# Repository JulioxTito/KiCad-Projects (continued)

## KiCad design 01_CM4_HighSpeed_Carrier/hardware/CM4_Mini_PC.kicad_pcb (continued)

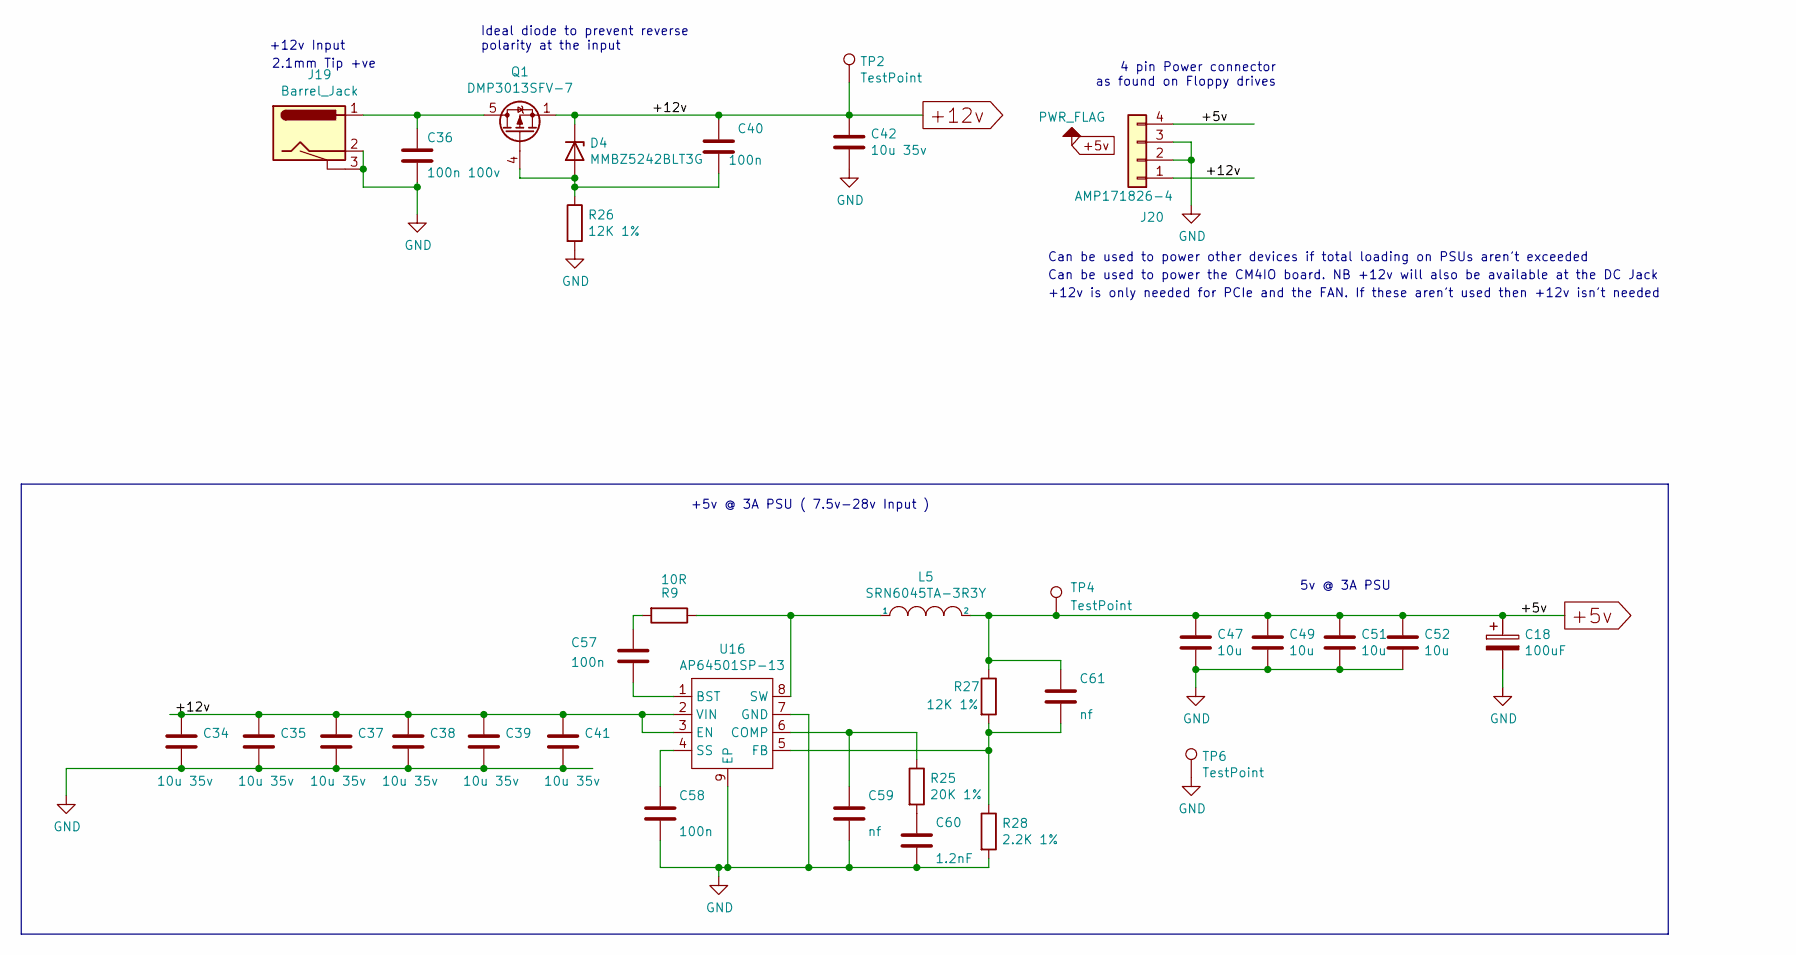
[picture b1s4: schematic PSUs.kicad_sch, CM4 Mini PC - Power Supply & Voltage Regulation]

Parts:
C18: 100uF; CP_EIA-7343-31_Kemet-D; Part Description Capacitor, SP-Cap, 100u, 6.3V, 15mR ESR
C34, C35, C37, C38, C39, C41, C42: 10u 35v; C_0805_2012Metric; Part Description 10uF 10% or 20% 35V Ceramic Capacitor X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
C36: 100n 100v; C_0402_1005Metric; Part Description 0.1uF 10% 100V Ceramic Capacitor X5R 04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
C40, C57, C58: 100n; C_0402_1005Metric; Part Description 0.1uF 10% 16V Ceramic Capacitor X7R 040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
C47, C49, C51, C52: 10u; C_0805_2012Metric; Part Description 10uF 10% 10V Ceramic Capacitor X7R 0805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
C59: nf; C_0402_1005Metric
C60: 1.2nF; C_0402_1005Metric; Part Description 1200pF 10% 10V Ceramic Capacitor X5R 04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
C61: nf; C_0402_1005Metric; Part Description 220 pF, 50 V, 0402 [1005 Metric], ± 5%,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
D4: MMBZ5242BLT3G; SOT-23; Part Description Zener Diode 12V 225mW 5% Surface Mount 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
J19: Barrel_Jack; BarrelJack_Horizontal; Part Description DC Power Connectors PCB 2.1MM
J20: AMP171826-4; PinHeader_1x04_P2.54mm_Vertical; Part Description Wire-To-Board Connector, Right Angle, 2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
L5: SRN6045TA-3R3Y; L_Bourns_SRN6045TA; Part Description 3.3µH Semi-Shielded Wirewound Inductor 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
Q1: DMP3013SFV-7; Diodes_PowerDI3333-8; Part Description DMP3013SFV-7 - Power MOSFET, P Channel,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
R9: 10R; R_0402_1005Metric; Part Description Resistor 10R M1005 1% 63mW
R25: 20K 1%; R_0402_1005Metric; Part Description Resistor 20K M1005 1% 63mW
R26, R27: 12K 1%; R_0402_1005Metric; Part Description Resistor 12K M1005 1% 63mW
R28: 2.2K 1%; R_0402_1005Metric; Part Description Resistor 2.2K M1005 1% 63mW
TP2, TP4, TP6: TestPoint; TestPoint_Pad_2.0x2.0mm
U16: AP64501SP-13; SOIC-8-1EP_3.9x4.9mm_P1.27mm_EP2.95x4.9mm_Mask2.71x3.4mm_Th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; Part Description Buck Switching Regulator IC Positive Ad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

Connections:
+5v: C18.1, C47.1, C49.1, C51.1, C52.1, C61.1, J20.4, L5.2, R27.1, TP4.1 (1_1); also elsewhere on the board
+12v: C34.1, C35.1, C37.1, C38.1, C39.1, C40.1, C41.1, C42.1, D4.1 (K), J20.1, Q1.1 (S), Q1.2 (S), Q1.3 (S), TP2.1 (1_1), U16.2 (VIN), U16.3 (EN); also elsewhere on the board
GND: C18.2, C34.2, C35.2, C36.2, C37.2, C38.2, C39.2, C41.2, C42.2, C47.2, C49.2, C51.2, C52.2, C58.2, C59.2, C60.2, J19.2, J19.3, J20.2, J20.3, R26.2, R28.2, TP6.1 (1_1), U16.7 (GND), U16.9 (EP); also elsewhere on the board
unnamed: C57.1, R9.2
unnamed: C60.1, R25.2
unnamed: C40.2, D4.2 (A), Q1.4 (G), R26.1
unnamed: C36.1, J19.1, Q1.5 (D)
unnamed: C57.2, U16.1 (BST)
unnamed: C59.1, R25.1, U16.6 (COMP)
unnamed: C61.2, R27.2, R28.1, U16.5 (FB)
unnamed: C58.1, U16.4 (SS)
unnamed: L5.1, R9.1, U16.8 (SW)

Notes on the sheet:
+12v Input
Can be used to power other devices if total loading on PSUs aren't exceeded
5v @ 3A PSU
+12v is only needed for PCIe and the FAN. If these aren't used then +12v isn't needed
Can be used to power the CM4IO board. NB +12v will also be available at the DC Jack
2.1mm Tip +ve
Ideal diode to prevent reverse polarity at the input
4 pin Power connector as found on Floppy drives
+5v @ 3A PSU ( 7.5v-28v Input )

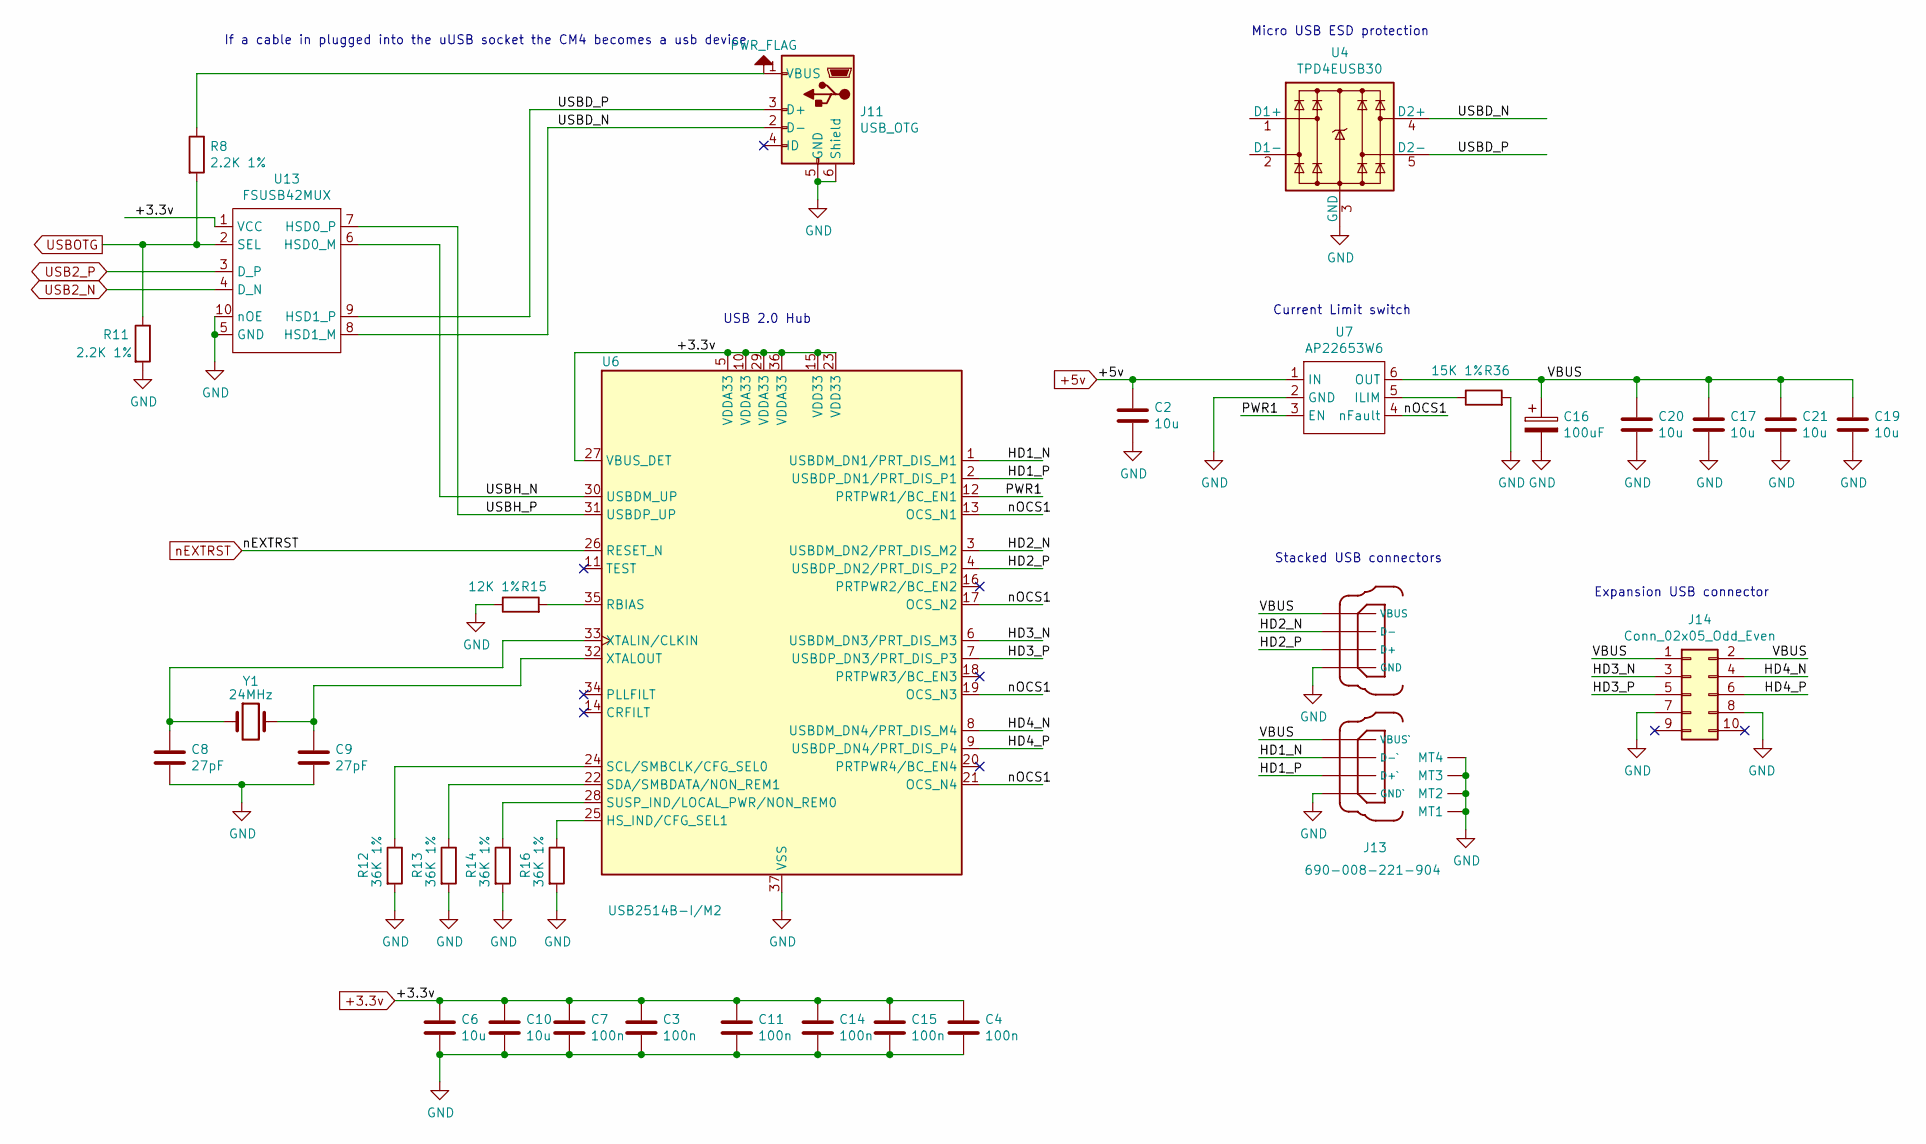
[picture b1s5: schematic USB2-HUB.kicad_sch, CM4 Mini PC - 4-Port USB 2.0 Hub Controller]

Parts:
C2, C6, C10, C17, C19, C20, C21: 10u; C_0805_2012Metric; Part Description 10uF 10% 10V Ceramic Capacitor X7R 0805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
C3, C4, C7, C11, C14, C15: 100n; C_0402_1005Metric; Part Description 0.1uF 10% 16V Ceramic Capacitor X7R 040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
C8, C9: 27pF; C_0402_1005Metric; Part Description 27pF 5% 50V Ceramic Capacitor C0G, NP0 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
C16: 100uF; CP_EIA-7343-31_Kemet-D; Part Description Capacitor, SP-Cap, 100u, 6.3V, 15mR ESR
J11: USB_OTG; USB_Micro-B_EDAC_UCON00686; Part Description USB - micro B USB 2.0 Receptacle Connec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
J13: 690-008-221-904; MOLEX_USB_67298-4090; Part Description USB-A (USB TYPE-A), Stacked Receptacle 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
J14: Conn_02x05_Odd_Even; PinHeader_2x05_P2.54mm_Vertical; Part Description PinHeader_2x05_P2.54mm_Vertical
R8, R11: 2.2K 1%; R_0402_1005Metric; Part Description Resistor 2.2K M1005 1% 63mW
R12, R13, R14, R16: 36K 1%; R_0402_1005Metric; Part Description Resistor 36K M1005 1% 63mW
R15: 12K 1%; R_0402_1005Metric; Part Description Resistor 12K M1005 1% 63mW
R36: 15K 1%; R_0402_1005Metric; Part Description Resistor 15K M1005 1% 63mW
U4: TPD4EUSB30; USON-10_2.5x1.0mm_P0.5mm; Part Description Quad TVS diode for high speed signals (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
U6: USB2514B-I/M2; QFN-36-1EP_6x6mm_P0.5mm_EP3.7x3.7mm; Part Description USB Hub Controller USB Interface 36-SQF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
U7: AP22653W6; SOT-23-6; Part Description Power Switch/Driver 1:1 P-Channel 2.1A 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
U13: FSUSB42MUX; MSOP-10_3x3mm_P0.5mm; Part Description USB Switch IC 1 Channel 10-MSOP
Y1: 24MHz; Crystal_SMD_HC49-SD; Part Description 24MHz Crystal 18pf 30ppm 30ppm

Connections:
+3.3v: C3.1, C4.1, C6.1, C7.1, C10.1, C11.1, C14.1, C15.1, U6.5 (VDDA33), U6.10 (VDDA33), U6.15 (VDD33), U6.23 (VDD33), U6.27 (VBUS_DET), U6.29 (VDDA33), U6.36 (VDDA33), U13.1 (VCC); also elsewhere on the board
+5v: C2.1, U7.1 (IN); also elsewhere on the board
/USB_Hub_Subsystem/HD1_N: J13.2 (D-`), U6.1 (USBDM_DN1/PRT_DIS_M1)
/USB_Hub_Subsystem/HD1_P: J13.3 (D+`), U6.2 (USBDP_DN1/PRT_DIS_P1)
/USB_Hub_Subsystem/HD2_N: J13.6 (D-), U6.3 (USBDM_DN2/PRT_DIS_M2)
/USB_Hub_Subsystem/HD2_P: J13.7 (D+), U6.4 (USBDP_DN2/PRT_DIS_P2)
/USB_Hub_Subsystem/HD3_N: J14.3, U6.6 (USBDM_DN3/PRT_DIS_M3)
/USB_Hub_Subsystem/HD3_P: J14.5, U6.7 (USBDP_DN3/PRT_DIS_P3)
/USB_Hub_Subsystem/HD4_N: J14.4, U6.8 (USBDM_DN4/PRT_DIS_M4)
/USB_Hub_Subsystem/HD4_P: J14.6, U6.9 (USBDP_DN4/PRT_DIS_P4)
/USB_Hub_Subsystem/PWR1: U6.12 (PRTPWR1/BC_EN1), U7.3 (EN)
/USB_Hub_Subsystem/USBD_N: J11.2 (D-), U4.4 (D2+), U4.7, U13.8 (HSD1_M)
/USB_Hub_Subsystem/USBD_P: J11.3 (D+), U4.5 (D2-), U4.6, U13.9 (HSD1_P)
/USB_Hub_Subsystem/USBH_N: U6.30 (USBDM_UP), U13.6 (HSD0_M)
/USB_Hub_Subsystem/USBH_P: U6.31 (USBDP_UP), U13.7 (HSD0_P)
/USB_Hub_Subsystem/VBUS: C16.1, C17.1, C19.1, C20.1, C21.1, J13.1 (VBUS`), J13.5 (VBUS), J14.1, J14.2, U7.6 (OUT)
/USB_Hub_Subsystem/nOCS1: U6.13 (OCS_N1), U6.17 (OCS_N2), U6.19 (OCS_N3), U6.21 (OCS_N4), U7.4 (nFault)
GND: C2.2, C3.2, C4.2, C6.2, C7.2, C8.2, C9.2, C10.2, C11.2, C14.2, C15.2, C16.2, C17.2, C19.2, C20.2, C21.2, J11.5 (GND), J11.6 (Shield), J13.4 (GND`), J13.8 (GND), J13.MT1, J13.MT2, J13.MT3, J13.MT4, J14.7, J14.8, R11.2, R12.2, R13.2, R14.2, R15.1, R16.2, R36.2, U4.3 (GND), U4.8 (GND), U6.37 (VSS), U7.2 (GND), U13.5 (GND), U13.10 (nOE); also elsewhere on the board
unnamed: J11.1 (VBUS), R8.1
unnamed: U4.1 (D1+), U4.10
unnamed: U4.2 (D1-), U4.9
unnamed: R16.1, U6.25 (HS_IND/CFG_SEL1)
unnamed: R15.2, U6.35 (RBIAS)
unnamed: R12.1, U6.24 (SCL/SMBCLK/CFG_SEL0)
unnamed: R13.1, U6.22 (SDA/SMBDATA/NON_REM1)
unnamed: R14.1, U6.28 (SUSP_IND/LOCAL_PWR/NON_REM0)
unnamed: C8.1, U6.33 (XTALIN/CLKIN), Y1.1
unnamed: C9.1, U6.32 (XTALOUT), Y1.2
unnamed: R36.1, U7.5 (ILIM)
USB2_N: U13.4 (D_N); also elsewhere on the board
USB2_P: U13.3 (D_P); also elsewhere on the board
USBOTG: R8.2, R11.1, U13.2 (SEL)
nEXTRST: U6.26 (RESET_N); also elsewhere on the board

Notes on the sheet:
Expansion USB connector
Current Limit switch
USB 2.0 Hub
If a cable in plugged into the uUSB socket the CM4 becomes a usb device
Micro USB ESD protection
Stacked USB connectors

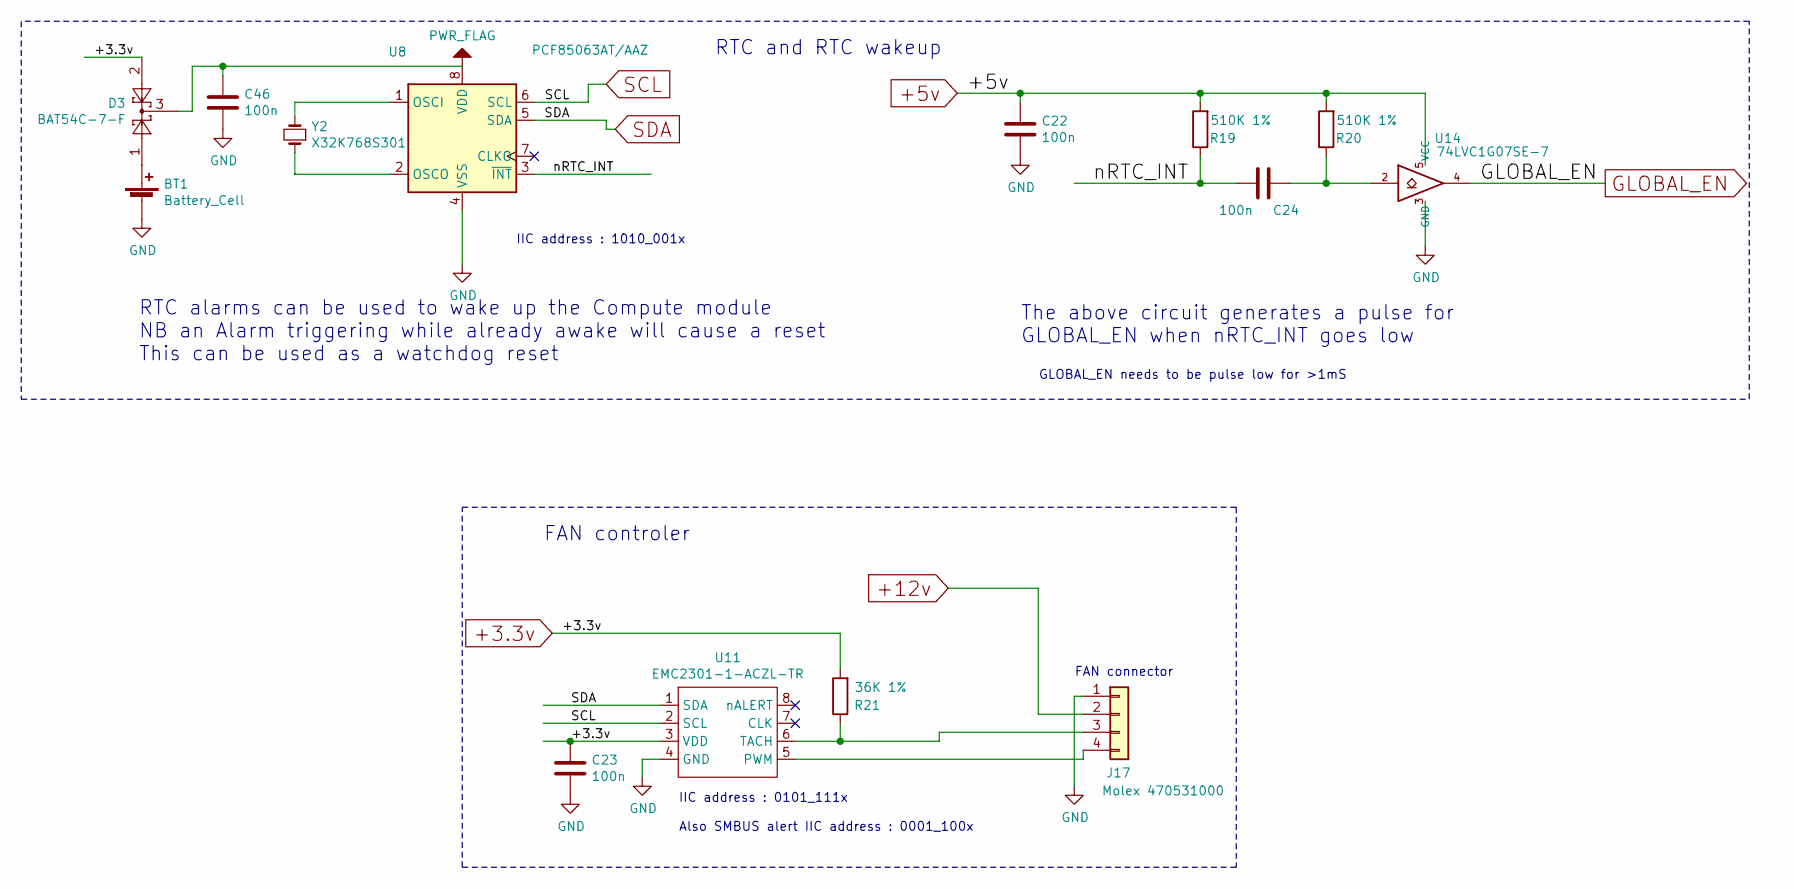
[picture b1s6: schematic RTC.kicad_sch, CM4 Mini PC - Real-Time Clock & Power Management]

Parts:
BT1: Battery_Cell; BatteryHolder_Keystone_3034_1x20mm; Part Description Battery Retainer Coin, 20.0mm 1 Cell SM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
C22, C23, C24, C46: 100n; C_0402_1005Metric; Part Description 0.1uF 10% 16V Ceramic Capacitor X7R 040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
D3: BAT54C-7-F; SOT-23; Part Description Diode Array 1 Pair Common Cathode Schot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
J17: Molex 470531000; FanPinHeader_1x04_P2.54mm_Vertical; Part Description Connector Header Through Hole 4 positio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
R19, R20: 510K 1%; R_0402_1005Metric; Part Description Resistor 510K M1005 1% 63mW
R21: 36K 1%; R_0402_1005Metric; Part Description Resistor 36K M1005 1% 63mW
U8: PCF85063AT/AAZ; SOIC-8_3.9x4.9mm_P1.27mm; Part Description Real Time Clock (RTC) IC Clock/Calendar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
U11: EMC2301-1-ACZL-TR; MSOP-8_3x3mm_P0.65mm; Part Description Motor Driver PWM 8-MSOP
U14: 74LVC1G07SE-7; SOT-353_SC-70-5; Part Description Buffer, Non-Inverting 1 Element 1 Bit p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
Y2: X32K768S301; Crystal_SMD_3215-2Pin_3.2x1.5mm; Part Description Crystal 32.768KHz 7pF 20pmm

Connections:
+3.3v: C23.1, D3.2, R21.2, U11.3 (VDD); also elsewhere on the board
+5v: C22.1, R19.2, R20.2, U14.5 (VCC); also elsewhere on the board
+12v: J17.2; also elsewhere on the board
/Real_Time_Clock/nRTC_INT: C24.2, R19.1, U8.3 (~INT)
GLOBAL_EN: U14.4; also elsewhere on the board
GND: BT1.2 (-), C22.2, C23.2, C46.2, J17.1, U8.4 (VSS), U11.4 (GND), U14.3 (GND); also elsewhere on the board
unnamed: BT1.1 (+), D3.1
unnamed: C24.1, R20.1, U14.2
unnamed: J17.3, R21.1, U11.6 (TACH)
unnamed: J17.4, U11.5 (PWM)
unnamed: U8.1 (OSCI), Y2.2
unnamed: U8.2 (OSCO), Y2.1
unnamed: C46.1, D3.3, U8.8 (VDD)
SCL: U8.6 (SCL), U11.2 (SCL)
SDA: U8.5 (SDA), U11.1 (SDA)

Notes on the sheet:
RTC alarms can be used to wake up the Compute module NB an Alarm triggering while already awake will cause a reset This can be used as a watchdog reset
RTC and RTC wakeup
Also SMBUS alert IIC address : 0001_100x
IIC address : 0101_111x
IIC address : 1010_001x
GLOBAL_EN needs to be pulse low for >1mS
FAN controler
FAN connector
The above circuit generates a pulse for GLOBAL_EN when nRTC_INT goes low

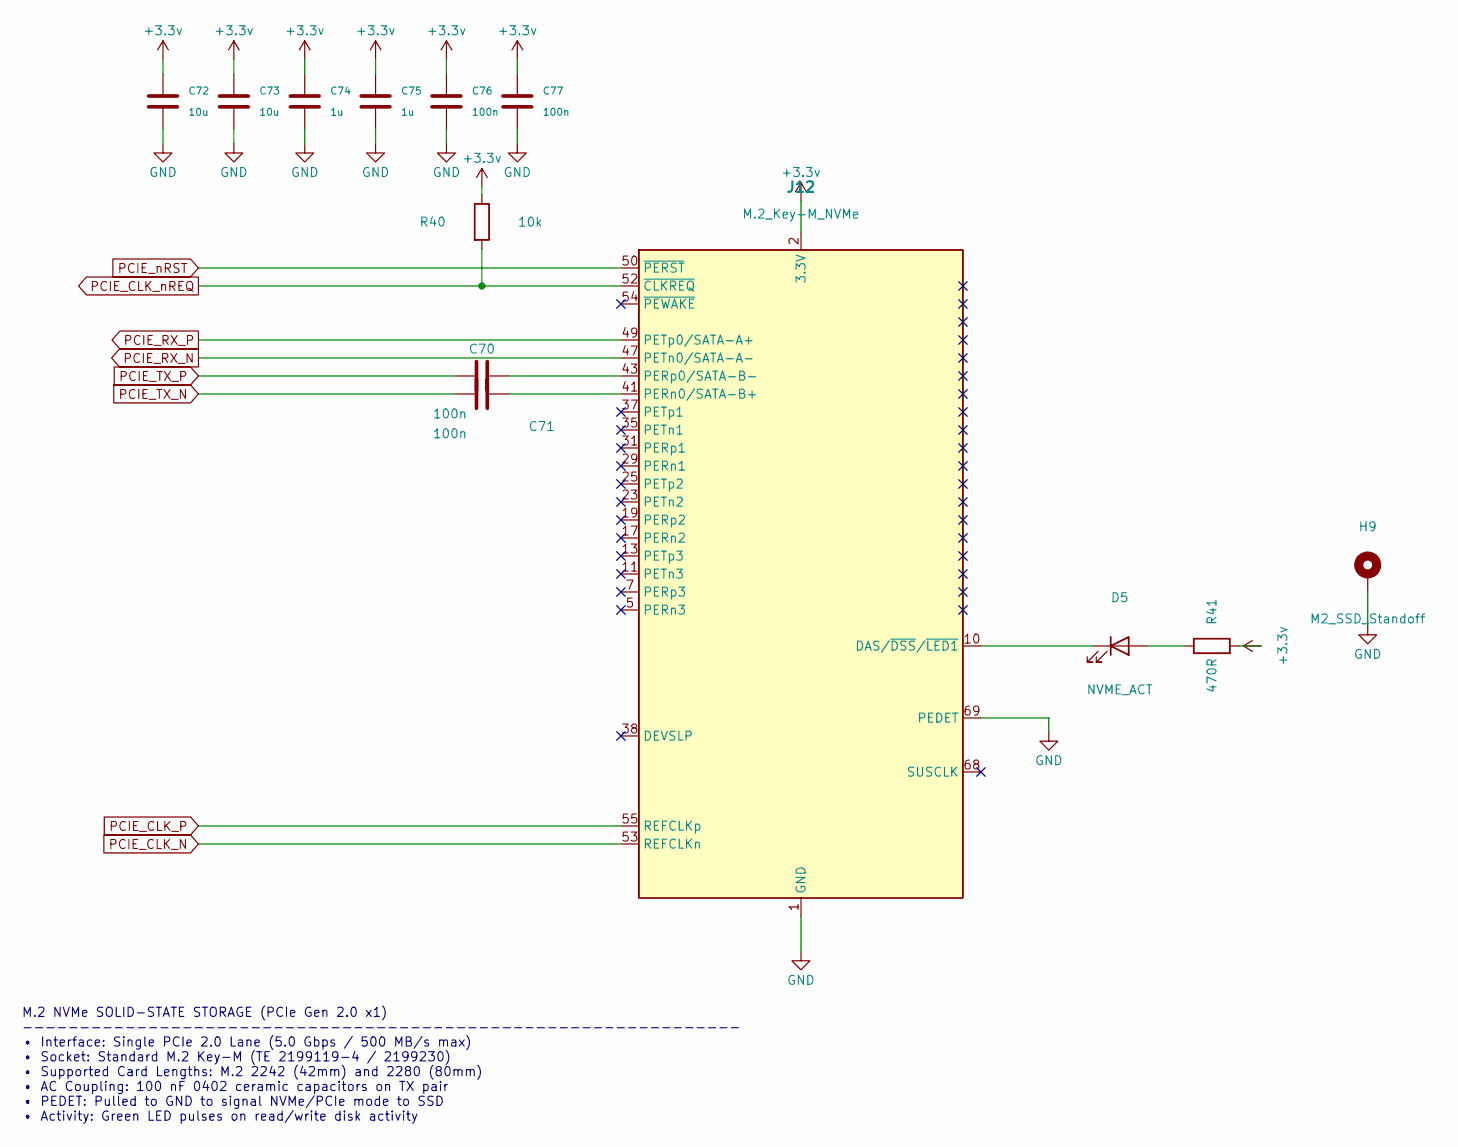
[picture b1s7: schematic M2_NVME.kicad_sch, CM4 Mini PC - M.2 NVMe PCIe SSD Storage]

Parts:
C70, C71, C76, C77: 100n; C_0402_1005Metric
C72, C73: 10u; C_0805_2012Metric
C74, C75: 1u; C_0603_1608Metric
D5: NVME_ACT; LED_0603_1608Metric
H9: M2_SSD_Standoff; MountingHole_2.2mm_M2_Pad
J12: M.2_Key-M_NVMe; TE_M.2_M_2x38-1MP_P0.5mm
R40: 10k; R_0402_1005Metric
R41: 470R; R_0402_1005Metric

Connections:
+3.3v: C72.1, C73.1, C74.1, C75.1, C76.1, C77.1, J12.2 (3.3V), J12.4 (3.3V), J12.12 (3.3V), J12.14 (3.3V), J12.16 (3.3V), J12.18 (3.3V), J12.70 (3.3V), J12.72 (3.3V), J12.74 (3.3V), R40.1, R41.2; also elsewhere on the board
GND: C72.2, C73.2, C74.2, C75.2, C76.2, C77.2, H9.1 (1_1), J12.1 (GND), J12.3 (GND), J12.9 (GND), J12.15 (GND), J12.21 (GND), J12.27 (GND), J12.33 (GND), J12.39 (GND), J12.45 (GND), J12.51 (GND), J12.57 (GND), J12.69 (PEDET), J12.71 (GND), J12.73 (GND), J12.75 (GND); also elsewhere on the board
unnamed: D5.2 (A), R41.1
unnamed: D5.1 (K), J12.10 (DAS/~DSS/~LED1)
unnamed: C71.2, J12.41 (PERn0/SATA-B+)
unnamed: C70.2, J12.43 (PERp0/SATA-B-)
PCIE_CLK_N: J12.53 (REFCLKn); also elsewhere on the board
PCIE_CLK_P: J12.55 (REFCLKp); also elsewhere on the board
PCIE_CLK_nREQ: J12.52 (~CLKREQ), R40.2; also elsewhere on the board
PCIE_RX_N: J12.47 (PETn0/SATA-A-); also elsewhere on the board
PCIE_RX_P: J12.49 (PETp0/SATA-A+); also elsewhere on the board
PCIE_TX_N: C71.1; also elsewhere on the board
PCIE_TX_P: C70.1; also elsewhere on the board
PCIE_nRST: J12.50 (~PERST); also elsewhere on the board

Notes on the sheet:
M.2 NVMe SOLID-STATE STORAGE (PCIe Gen 2.0 x1) --------------------------------------------------------------- • Interface: Single PCIe 2.0 Lane (5.0 Gbps / 500 MB/s max) • Socket: Standard M.2 Key-M (TE 2199119-4 / 2199230) • Supported Card Lengths: M.2 2242 (42mm) and 2280 (80mm) • AC Coupling: 1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

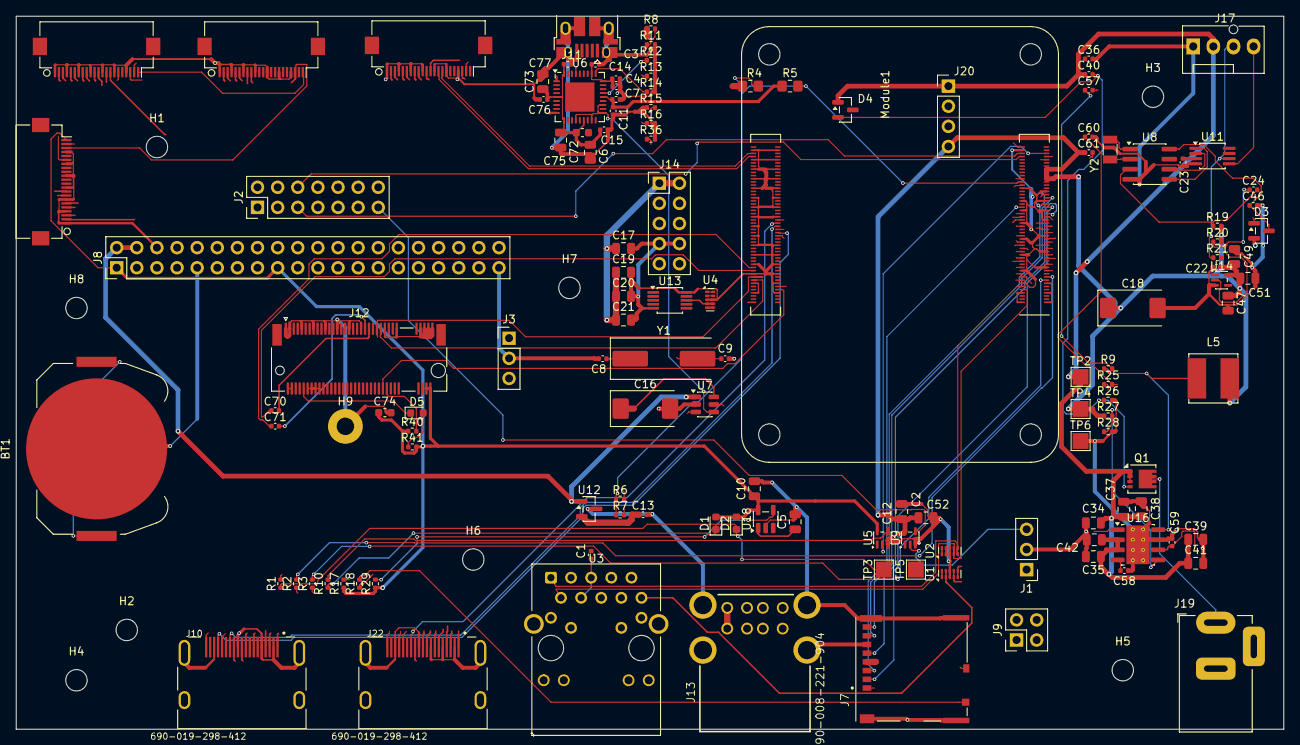
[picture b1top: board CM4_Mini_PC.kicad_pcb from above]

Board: 4 copper layers, 160.0 x 90.0 mm, 139 parts (0 on the bottom side), 202 nets.

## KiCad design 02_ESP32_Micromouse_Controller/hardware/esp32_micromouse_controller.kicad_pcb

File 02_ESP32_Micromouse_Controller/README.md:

# ESP32-S3 Micromouse Robot Controller

<p align="center">
  <em>Figure 1: (Left) High-resolution raytraced 3D isometric perspective showing the ESP32-S3 module, USB-C port, and headers. (Right) KiCad PCB Editor layout with ground plane flood and thermal relief spokes.</em>
</p>

<p align="center">
  <em>Figure 2: (Left) Top orthogonal assembly layout. (Right) Bottom ground plane flood with thermal relief spoke connections.</em>
</p>

<p align="center">
  
  <br>
  <em>Figure 3: Rear isometric perspective illustrating chassis mounting clearances, motor driver header, and sensor breakouts.</em>
</p>

## 📌 Project Summary
A custom 2-layer autonomous robotics motherboard engineered for an IEEE Micromouse competition robot. Powered by the **ESP32-S3** dual-core microcontroller with onboard Wi-Fi and Bluetooth LE, this board integrates dual high-efficiency H-bridge motor drivers, optical quadrature encoder interfaces, multi-channel infrared distance sensor headers, and onboard DC-DC buck regulation.

---

## 📐 Key Specifications
* **Microcontroller**: Espressif ESP32-S3-WROOM-1 (240 MHz dual-core Xtensa LX7, 512 KB SRAM, 8 MB Flash).
* **Motor Drive Architecture**: Dual integrated H-bridge drivers capable of bidirectional PWM speed and direction control.
* **Sensor Interfaces**:
  * 4x IR distance sensor analog inputs with filtered reference rails.
  * Dual optical quadrature encoder inputs for closed-loop odometry and PID trajectory tracking.
* **Power Management**:
  * 2S LiPo battery input ($7.4\text{ V} - 8.4\text{ V}$).
  * High-efficiency DC-DC step-down buck converter delivering stable $+3.3\text{ V}$ and $+5.0\text{ V}$ logic rails.
* **Connectivity & Debug**: USB Type-C interface with dual 5.1 kΩ CC pull-down resistors for native USB serial/JTAG flashing.
* **Layer Count**: 2 Layers (Top Component/Signal + Bottom Ground Pour).

---

## 📁 Project Directory Contents
* [`hardware/`](hardware/): KiCad project files (`esp32_micromouse_controller.kicad_pro`), schematics, PCB layout, and production Gerbers.
* [`images/board_iso_front.png`](images/board_iso_front.png): High-resolution raytraced 3D isometric render.
* [`images/board_layout.png`](images/board_layout.png): KiCad PCB Editor layout artwork.
* [`images/board_top_3d.png`](images/board_top_3d.png): Top-down 3D orthogonal view.
* [`images/board_bottom_3d.png`](images/board_bottom_3d.png): Bottom ground plane 3D view.
* [`images/board_iso_back.png`](images/board_iso_back.png): Reverse angle 3D view.
* [`images/ESP32_Micromouse_Schematic.pdf`](images/ESP32_Micromouse_Schematic.pdf): Complete schematic diagram.

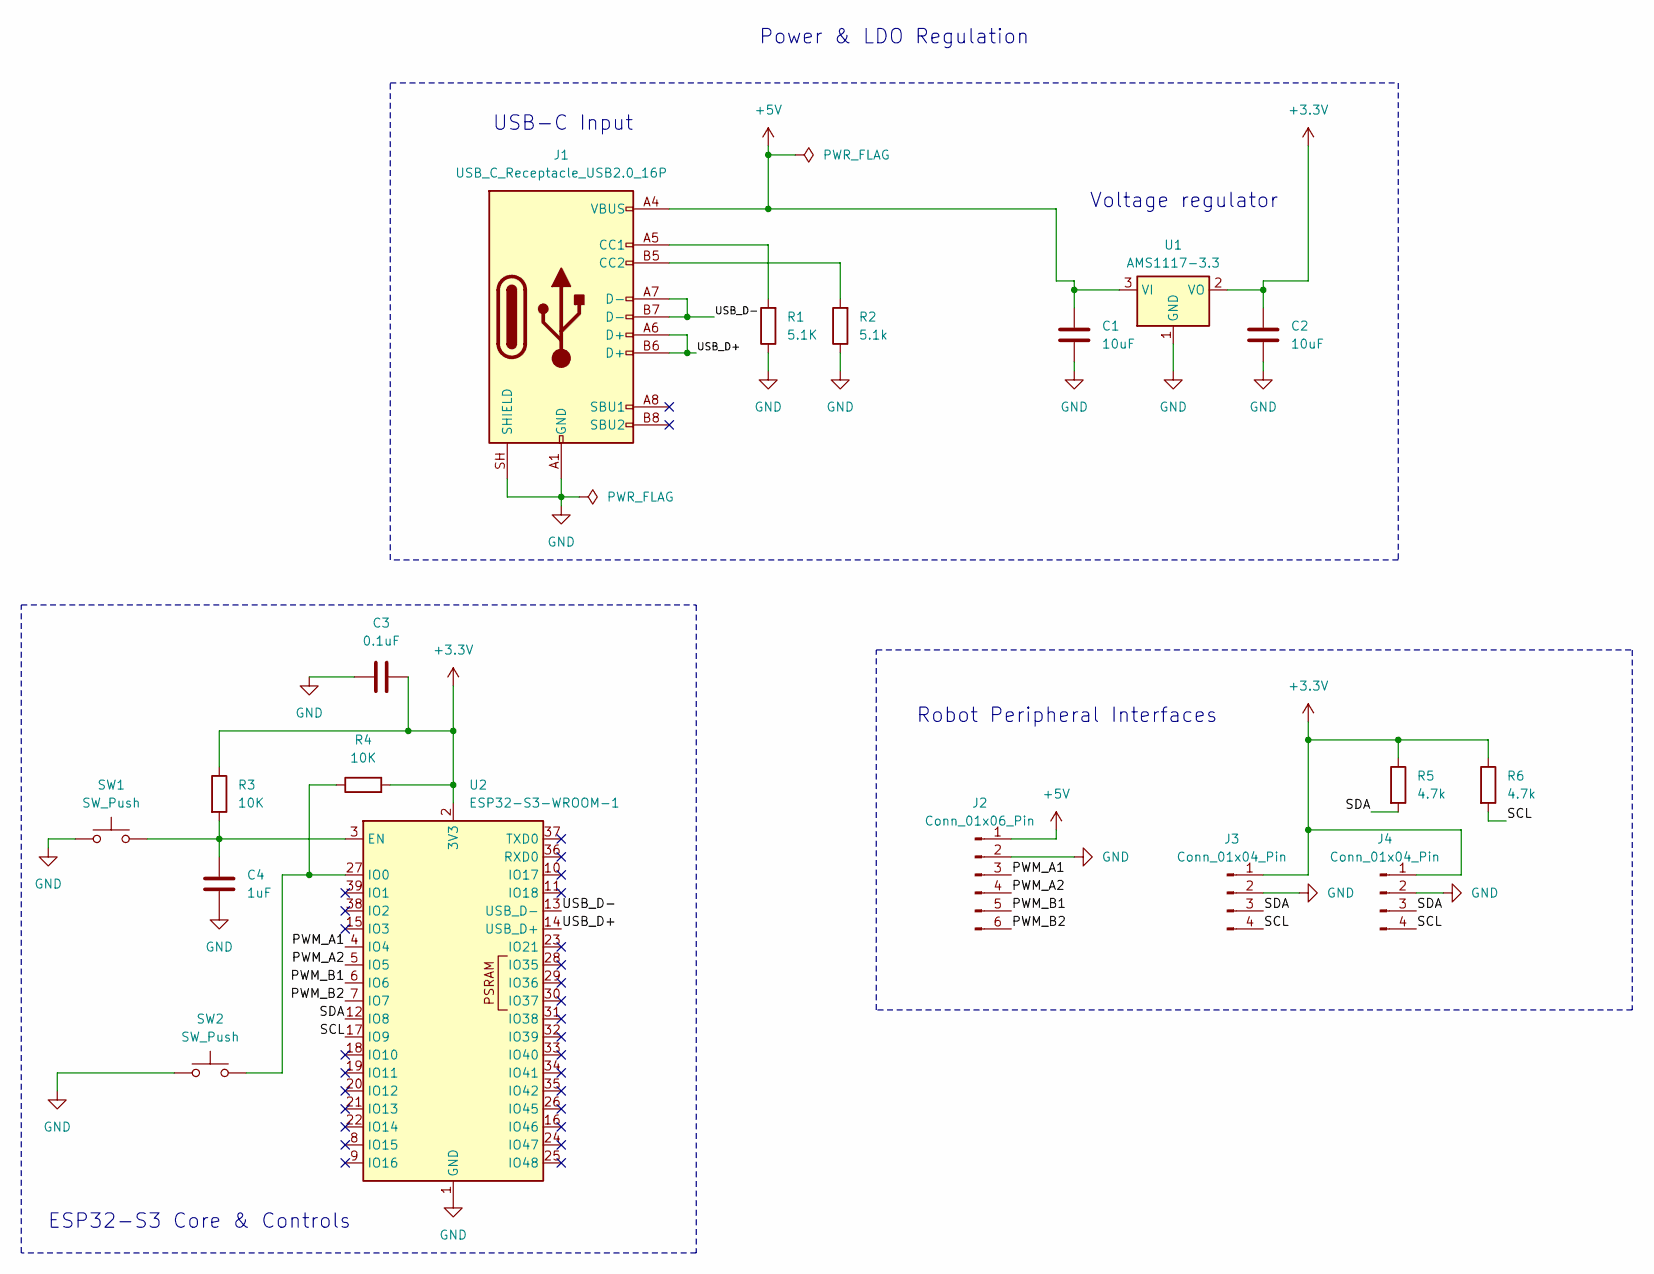
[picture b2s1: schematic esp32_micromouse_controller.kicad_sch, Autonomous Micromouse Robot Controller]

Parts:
C1, C2: 10uF; C_0805_2012Metric
C3: 0.1uF; C_0805_2012Metric
C4: 1uF; C_0805_2012Metric
J1: USB_C_Receptacle_USB2.0_16P; USB_C_Receptacle_HRO_TYPE-C-31-M-12
J2: Conn_01x06_Pin; PinHeader_1x06_P2.54mm_Vertical
J3, J4: Conn_01x04_Pin; PinHeader_1x04_P2.54mm_Vertical
R1: 5.1K; R_0805_2012Metric
R2: 5.1k; R_0805_2012Metric
R3, R4: 10K; R_0805_2012Metric
R5, R6: 4.7k; R_0805_2012Metric
SW1, SW2: SW_Push; SW_PUSH_6mm
U1: AMS1117-3.3; SOT-223-3_TabPin2
U2: ESP32-S3-WROOM-1

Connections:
+3.3V: C2.1, C3.1, J3.1, J4.1, R3.1, R4.2, R5.1, R6.1, U1.2 (VO), U2.2 (3V3)
+5V: C1.1, J1.A4 (VBUS), J1.A9 (VBUS), J1.B4 (VBUS), J1.B9 (VBUS), J2.1, U1.3 (VI)
/PWM_A1: J2.3, U2.4 (IO4)
/PWM_A2: J2.4, U2.5 (IO5)
/PWM_B1: J2.5, U2.6 (IO6)
/PWM_B2: J2.6, U2.7 (IO7)
/SCL: J3.4, J4.4, R6.2, U2.17 (IO9)
/SDA: J3.3, J4.3, R5.2, U2.12 (IO8)
/USB_D+: J1.A6 (D+), J1.B6 (D+), U2.14 (USB_D+)
/USB_D-: J1.A7 (D-), J1.B7 (D-), U2.13 (USB_D-)
GND: C1.2, C2.2, C3.2, C4.2, J1.A1 (GND), J1.A12 (GND), J1.B1 (GND), J1.B12 (GND), J1.SH (SHIELD), J2.2, J3.2, J4.2, R1.1, R2.1, SW1.1, SW2.1, U1.1 (GND), U2.1 (GND), U2.40 (GND), U2.41 (GND)
unnamed: J1.A5 (CC1), R1.2
unnamed: J1.B5 (CC2), R2.2
unnamed: C4.1, R3.2, SW1.2, U2.3 (EN)
unnamed: R4.1, SW2.2, U2.27 (IO0)

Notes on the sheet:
Power & LDO Regulation
ESP32-S3 Core & Controls
USB-C Input
Robot Peripheral Interfaces
Voltage regulator

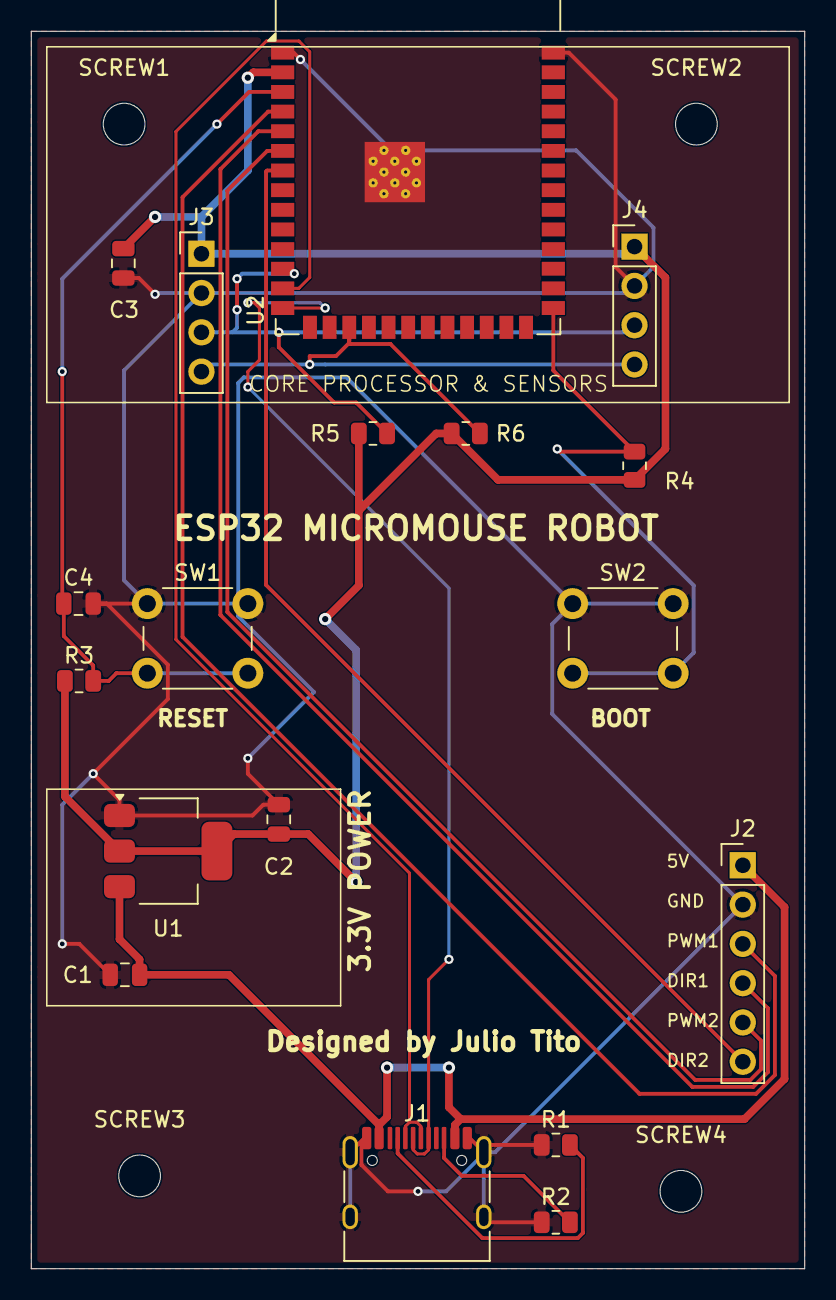
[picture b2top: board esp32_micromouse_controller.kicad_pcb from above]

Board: 2 copper layers, 50.0 x 80.0 mm, 22 parts (0 on the bottom side), 15 nets.

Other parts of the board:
SCREW1, SCREW2, SCREW3, SCREW4: MountingHole_2.7mm_M2.5

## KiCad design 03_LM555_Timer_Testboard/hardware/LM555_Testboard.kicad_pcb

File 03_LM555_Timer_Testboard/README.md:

# LM555 Precision Timer Testboard

<p align="center">
  <em>Figure 1: (Left) Raytraced 3D model with balanced camera perspective and floor reflections. (Right) KiCad PCB Editor layout showing traces, pads, and component silkscreen.</em>
</p>

### 📸 Multi-Angle 3D Hardware Perspectives

<p align="center">
  <em>Figure 2: (Left) Rear isometric angle showing timing potentiometer and output stage. (Right) Low-angle profile perspective.</em>
</p>

<p align="center">
  <em>Figure 3: (Left) Orthogonal Top 3D view showing DIP-8 socket, passives, and test loops. (Right) Bottom ground plane flood.</em>
</p>

---

## 📌 Project Summary
A precision analog timing and waveform generation testboard built around the industry-standard **LM555 / NE555** bipolar timer IC. Designed as an educational and hardware validation platform, it allows hands-on characterization of astable multivibrators, frequency tuning, pulse-width modulation (PWM), and transient response.

---

## 📐 Key Specifications & Circuit Physics
* **Timer IC**: LM555 / NE555 Timer in standard 8-pin DIP package with socket header.
* **Oscillator Mode**: Astable Multivibrator configuration generating continuous square-wave output.
* **Frequency Calculation**:
  $$f = \frac{1.44}{(R_1 + 2R_2) C}$$
  $$T_H = 0.693 \cdot (R_1 + R_2) \cdot C, \quad T_L = 0.693 \cdot R_2 \cdot C$$
  $$\text{Duty Cycle} = \frac{R_1 + R_2}{R_1 + 2R_2} \times 100\%$$
* **User Feedback & Indicators**:
  * Transistor-buffered output LED for visual pulse frequency verification.
  * Dedicated high-impedance oscilloscope test points (GND, TRIG, THRES, OUT, VCC).
* **Decoupling Network**: Low-ESR ceramic decoupling capacitors on Pin 5 ($0.01\,\mu\text{F}$) for noise immunity on the internal $2/3\,V_{CC}$ comparator threshold.
* **Layer Count**: 2 Layers (Top Signal/Power, Bottom Ground Plane).

---

## 📁 Project Directory Contents
* [`hardware/`](hardware/): KiCad project files (`LM555_Testboard.kicad_pro`), schematics, PCB layout, and bill of materials (`LM555_Testboard.csv`).
* [`images/lm555_3d_render.png`](images/lm555_3d_render.png): High-resolution raytraced 3D render.
* [`images/lm555_pcb_layout.png`](images/lm555_pcb_layout.png): KiCad PCB Editor layout artwork.
* [`images/lm555_3d_top.png`](images/lm555_3d_top.png): Top orthogonal 3D view.
* [`images/LM555_Timer_Schematic.pdf`](images/LM555_Timer_Schematic.pdf): Complete schematic diagram.

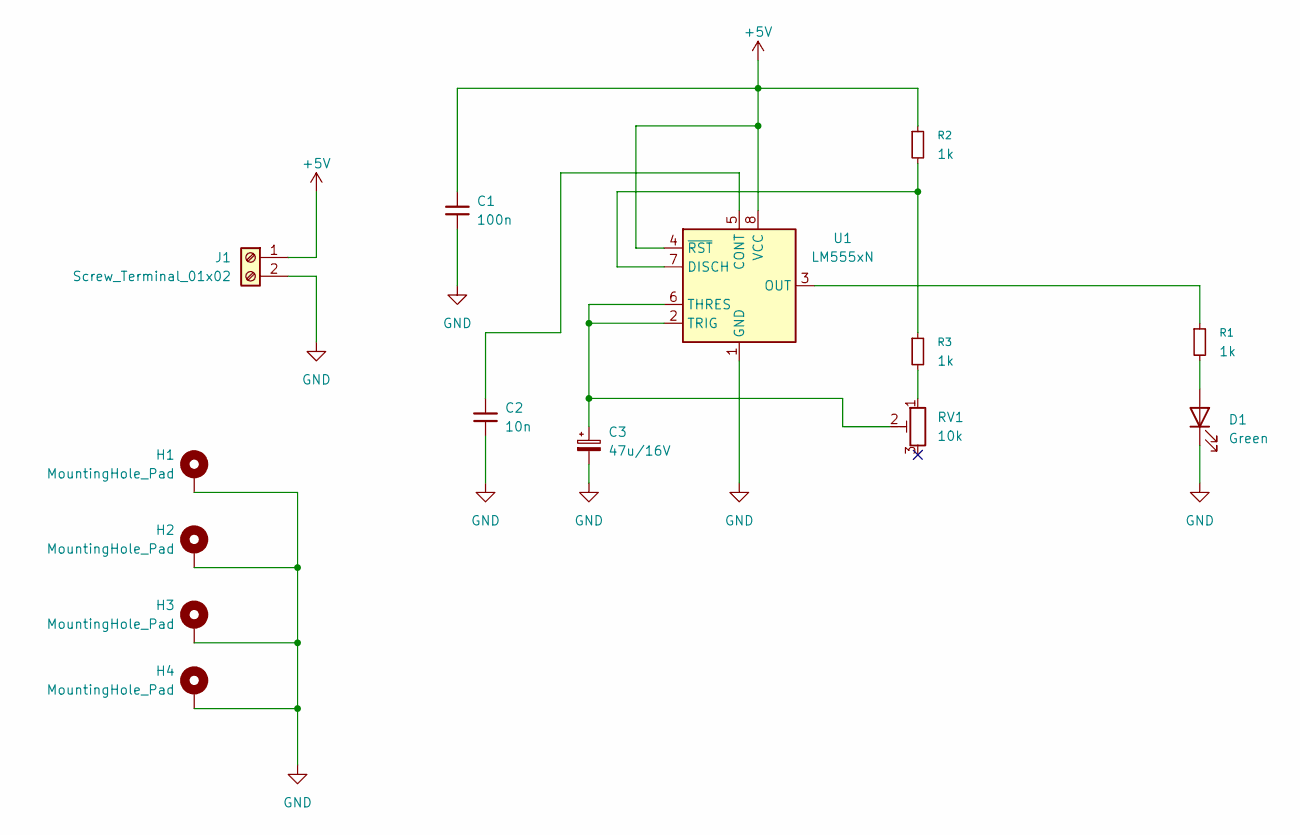
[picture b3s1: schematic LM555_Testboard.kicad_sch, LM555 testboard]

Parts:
C1: 100n; C_Disc_D7.0mm_W2.5mm_P5.00mm
C2: 10n; C_Disc_D7.0mm_W2.5mm_P5.00mm
C3: 47u/16V; CP_Radial_D5.0mm_P2.00mm
D1: Green; LED_D3.0mm
H1, H2, H3, H4: MountingHole_Pad; MountingHole_3.2mm_M3_DIN965_Pad
J1: Screw_Terminal_01x02; TerminalBlock_Phoenix_PT-1,5-2-3.5-H_1x02_P3.50mm_Horizontal
R1, R2, R3: 1k; R_Axial_DIN0207_L6.3mm_D2.5mm_P10.16mm_Horizontal
RV1: 10k; Potentiometer_Bourns_3386P_Vertical
U1: LM555xN; DIP-8_W7.62mm

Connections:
+5V: C1.1, J1.1, R2.1, U1.4 (~RST), U1.8 (VCC)
GND: C1.2, C2.2, C3.2, D1.1 (K), H1.1 (1_1), H2.1 (1_1), H3.1 (1_1), H4.1 (1_1), J1.2, U1.1 (GND)
unnamed: D1.2 (A), R1.2
unnamed: R3.2, RV1.1
unnamed: C2.1, U1.5 (CONT)
unnamed: R2.2, R3.1, U1.7 (DISCH)
unnamed: R1.1, U1.3 (OUT)
unnamed: C3.1, RV1.2, U1.2 (TRIG), U1.6 (THRES)

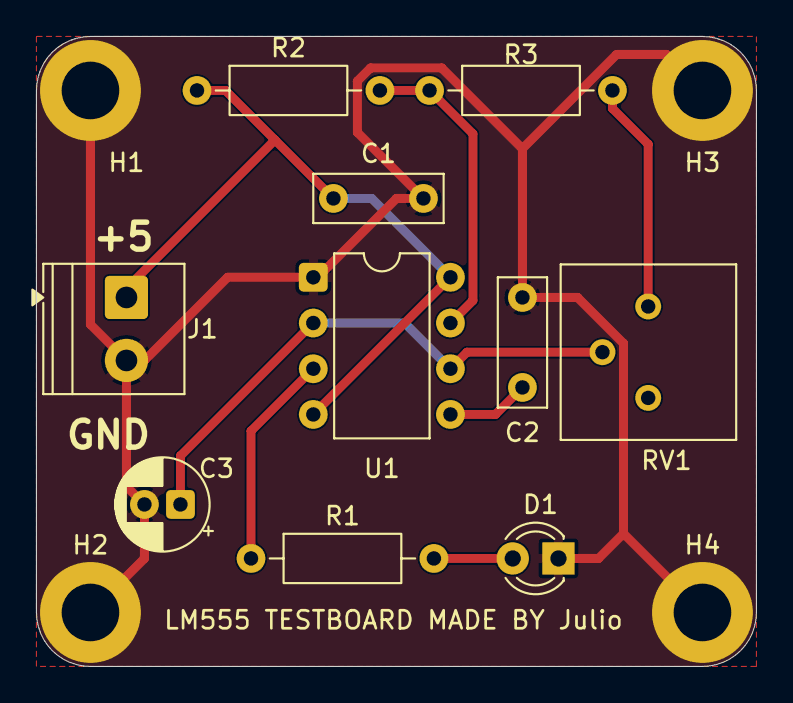
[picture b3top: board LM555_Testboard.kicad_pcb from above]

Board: 2 copper layers, 40.0 x 35.0 mm, 14 parts (0 on the bottom side), 8 nets.
